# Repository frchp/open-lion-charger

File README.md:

# open-lion-charger
Open source battery charger and discharger

Based on [private archived project](https://github.com/frchp/li-ion-battery-high-current-charger)

TODO :
  1. Manufacturing
  2. Arduino software/library for easy integration

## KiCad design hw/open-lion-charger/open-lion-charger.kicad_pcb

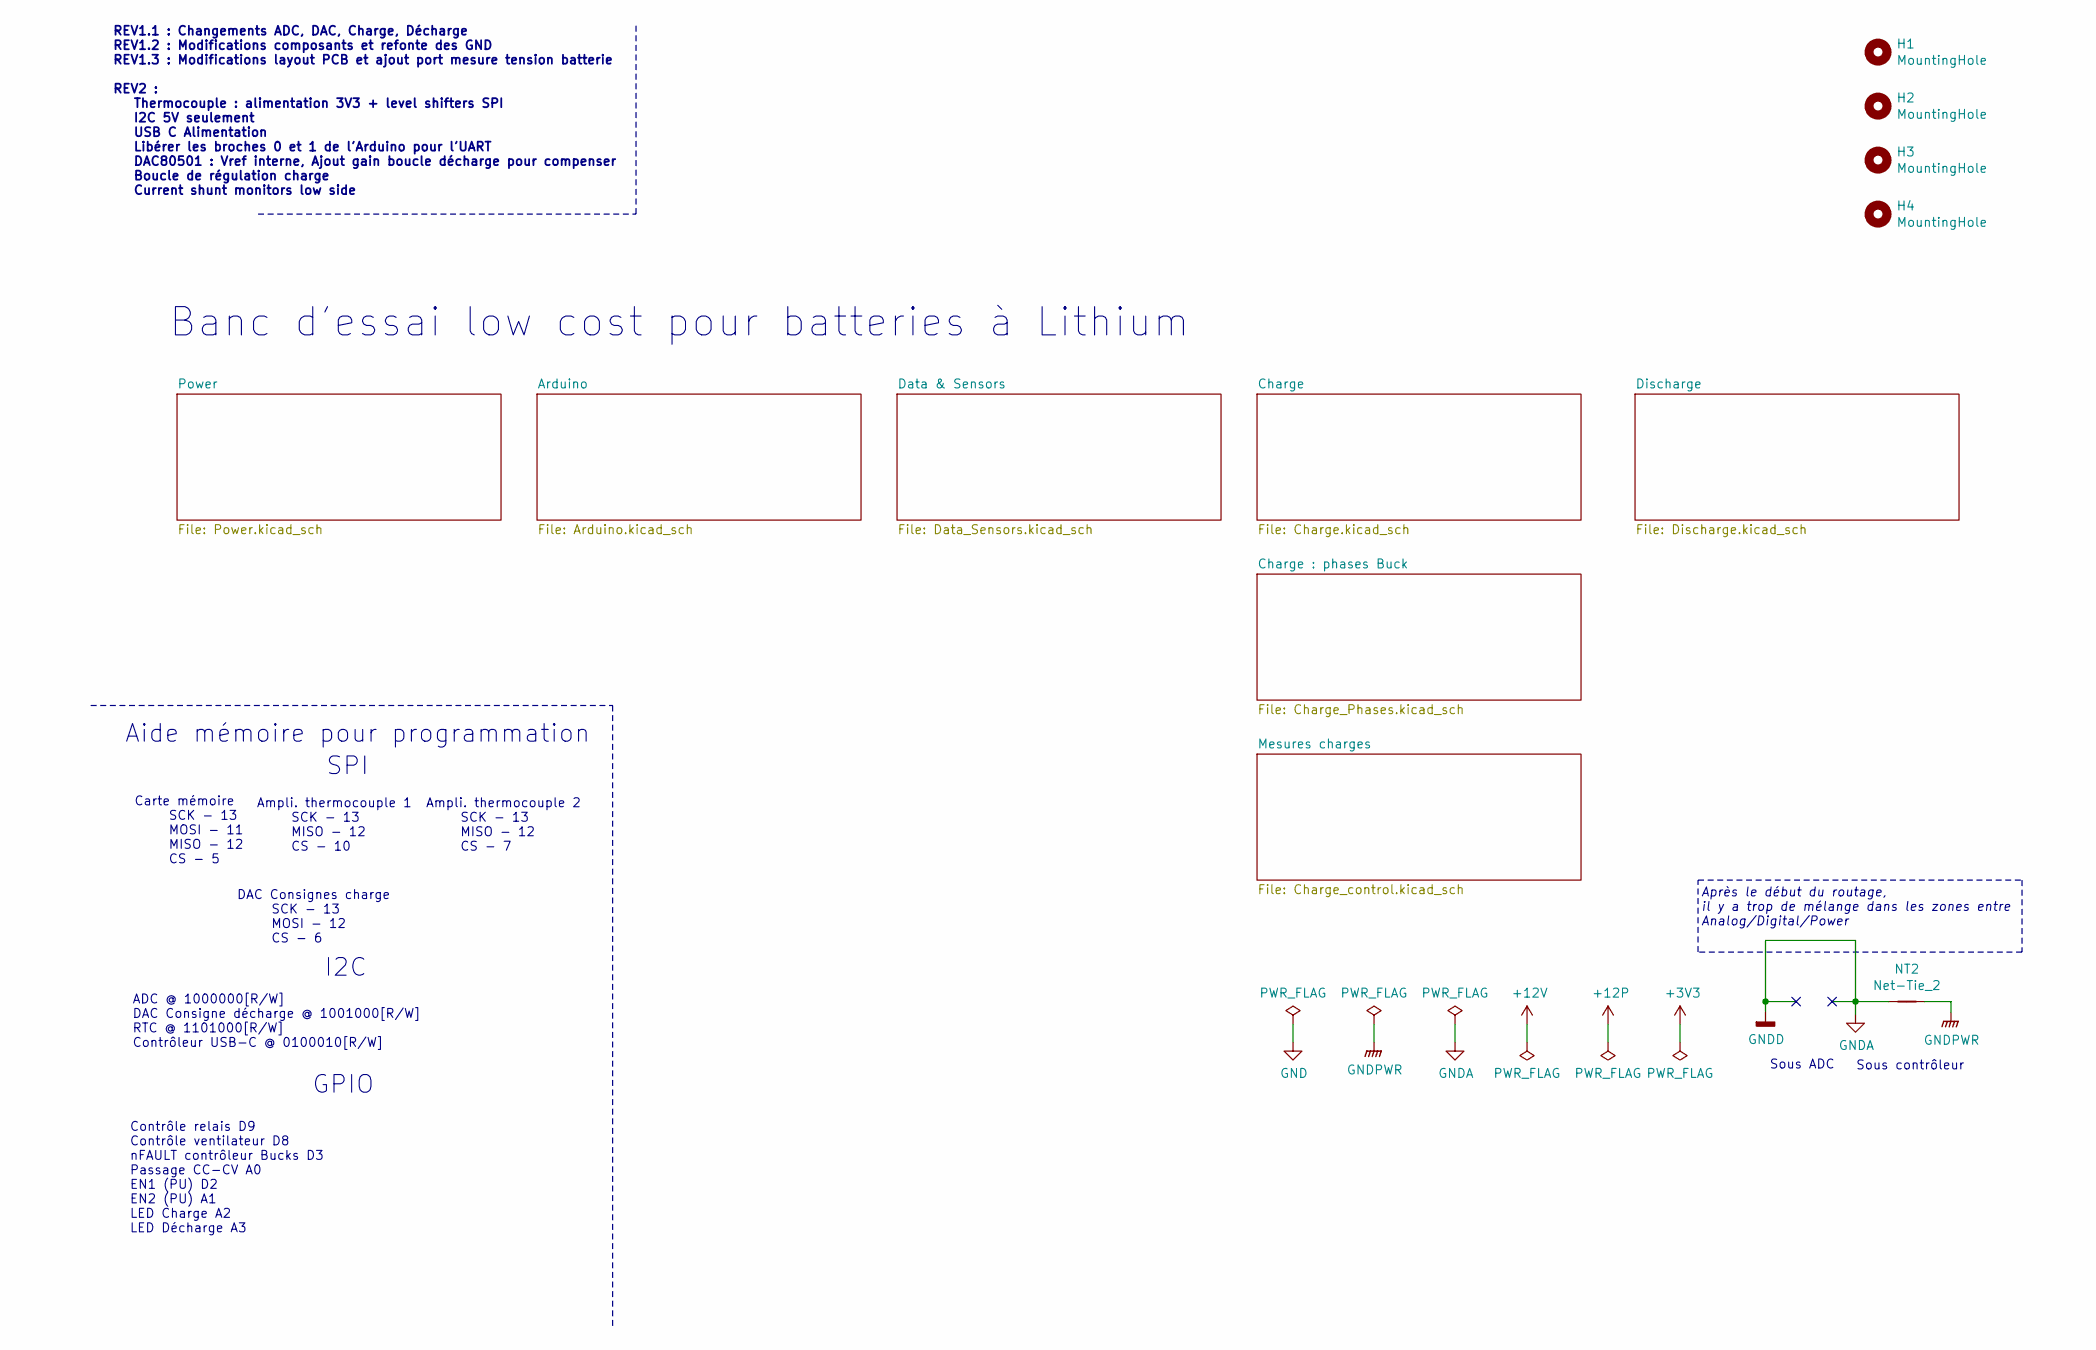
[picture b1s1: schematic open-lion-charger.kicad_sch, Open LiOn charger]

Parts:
H1, H2, H3, H4: MountingHole; MountingHole_3.2mm_M3_ISO7380
NT2: Net-Tie_2; NetTie-2_SMD_Pad0.5mm

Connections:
GNDA: NT2.1; also elsewhere on the board
GNDPWR: NT2.2; also elsewhere on the board

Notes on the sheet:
Carte mémoire SCK - 13 MOSI - 11 MISO - 12 CS - 5
Ampli. thermocouple 1 SCK - 13 MISO - 12 CS - 10
I2C
Ampli. thermocouple 2 SCK - 13 MISO - 12 CS - 7
REV1.1 : Changements ADC, DAC, Charge, Décharge REV1.2 : Modifications composants et refonte des GND REV1.3 : Modifications layout PCB et ajout port mesure tension batterie REV2 : Thermocouple : alimentation 3V3 + level shifters SPI I2C 5V seulement USB C Alimentation Libérer les broches 0 et 1 de 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
GPIO
Sous contrôleur
DAC Consignes charge SCK - 13 MOSI - 12 CS - 6
Aide mémoire pour programmation
ADC @ 1000000[R/W] DAC Consigne décharge @ 1001000[R/W] RTC @ 1101000[R/W] Contrôleur USB-C @ 0100010[R/W]
Sous ADC
SPI
Contrôle relais D9 Contrôle ventilateur D8 nFAULT contrôleur Bucks D3 Passage CC-CV A0 EN1 (PU) D2 EN2 (PU) A1 LED Charge A2 LED Décharge A3
Après le début du routage, il y a trop de mélange dans les zones entre Analog/Digital/Power
Banc d'essai low cost pour batteries à Lithium

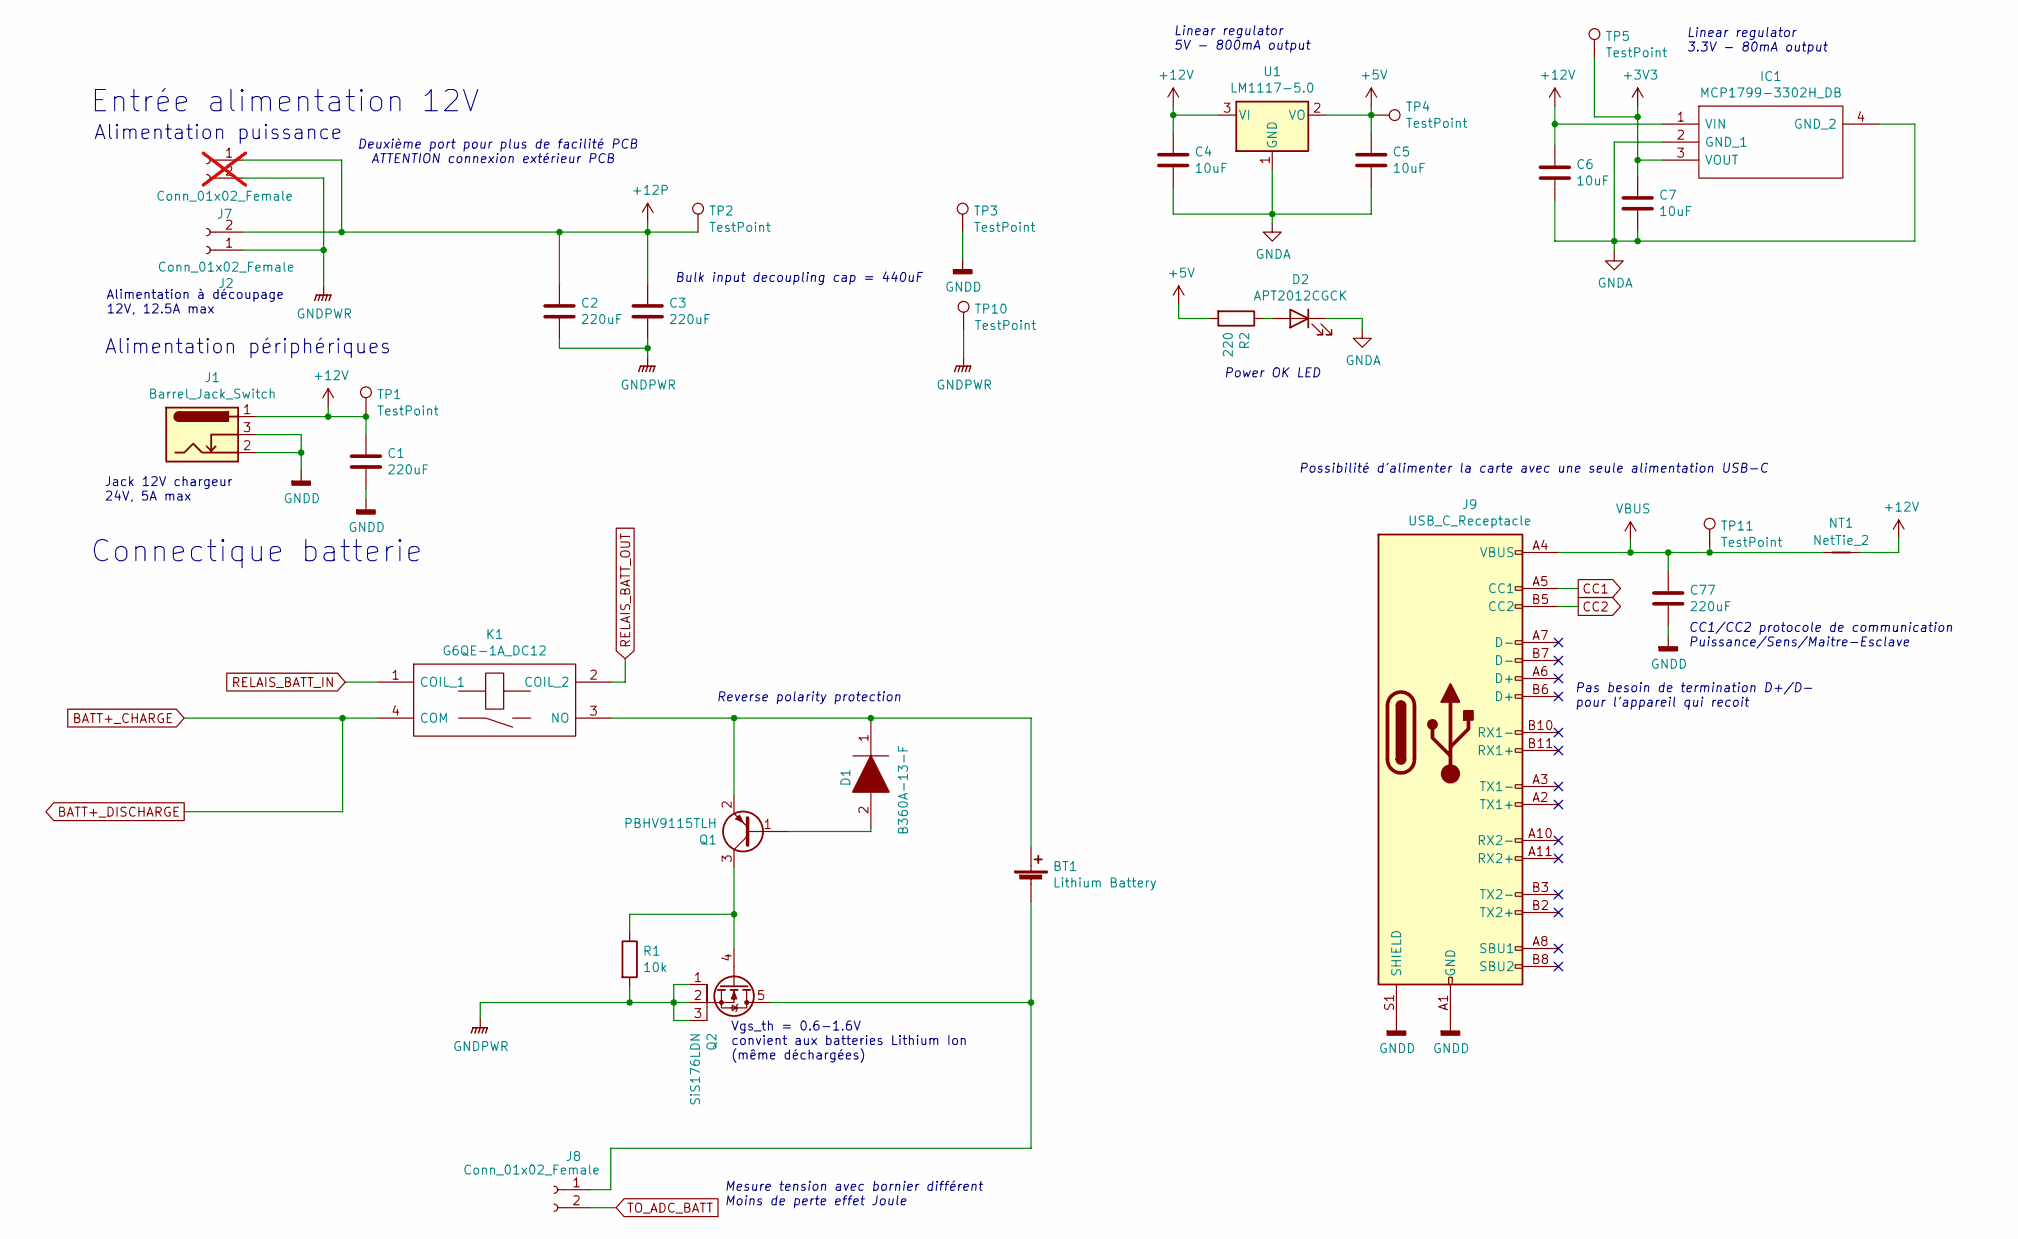
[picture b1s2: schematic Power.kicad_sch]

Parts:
BT1: Lithium Battery; TerminalBlock_bornier-2_P5.08mm
C1, C2, C3, C77: 220uF; CP_EIA-7343-31_Kemet-D_Pad2.25x2.55mm_HandSolder
C4, C5, C6, C7: 10uF; C_0805_2012Metric
D1: B360A-13-F; DIOM5226X240N; Manufacturer_Part_Number B360A-13-F; Mouser Part Number 621-B360A-F
D2: APT2012CGCK; LED_0805_2012Metric_Pad1.15x1.40mm_HandSolder
IC1: MCP1799-3302H_DB; SOT230P700X180-4N; Manufacturer_Part_Number MCP1799-3302H/DB; Mouser Part Number 579-MCP1799-3302H/DB
J1: Barrel_Jack_Switch; BarrelJack_Wuerth_6941xx301002
J2, J8: Conn_01x02_Female; TerminalBlock_bornier-2_P5.08mm
J7: Conn_01x02_Female; TerminalBlock_bornier-2_P5.08mm; not fitted
J9: USB_C_Receptacle; USB_C_Receptacle_GCT_USB4085
K1: G6QE-1A_DC12; G6QE1ADC12; Manufacturer_Part_Number G6QE-1A DC12; Mouser Part Number 653-G6QE-1ADC12
NT1: NetTie_2; R_2816_7142Metric_Pad3.20x4.45mm_HandSolder
Q1: PBHV9115TLH; SOT-23
Q2: SiS176LDN; Vishay_PowerPAK_1212-8_Single
R1: 10k; R_0805_2012Metric
R2: 220; R_0805_2012Metric
TP1, TP2, TP3, TP4, TP5, TP10, TP11: TestPoint; TestPoint_Keystone_5000-5004_Miniature
U1: LM1117-5.0; SOT-223

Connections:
+3V3: C7.1, IC1.3 (VOUT), TP5.1; also elsewhere on the board
+5V: C5.1, R2.2, TP4.1, U1.2 (VO); also elsewhere on the board
+12P: C2.1, C3.1, J2.2, J7.1, TP2.1; also elsewhere on the board
BATT+_CHARGE: K1.4 (COM); also elsewhere on the board
CC1: J9.A5 (CC1); also elsewhere on the board
CC2: J9.B5 (CC2); also elsewhere on the board
GNDA: C1.2, C4.2, C5.2, C6.2, C7.2, C77.2, D2.1 (K), IC1.2 (GND_1), IC1.4 (GND_2), J1.2, J1.3, J9.A1 (GND), J9.A12 (GND), J9.B1 (GND), J9.B12 (GND), J9.S1 (SHIELD), TP3.1, U1.1 (GND); also elsewhere on the board
GNDPWR: C2.2, C3.2, J2.1, J7.2, Q2.1, Q2.2, Q2.3, R1.2, TP10.1; also elsewhere on the board
unnamed: BT1.1 (+), D1.1, K1.3 (NO), Q1.2 (E)
unnamed: BT1.2 (-), J8.1, Q2.5
unnamed: D2.2 (A), R2.1
unnamed: D1.2, Q1.1 (B)
unnamed: Q1.3 (C), Q2.4, R1.1
RELAIS_BATT_IN: K1.1 (COIL_1); also elsewhere on the board
RELAIS_BATT_OUT: C1.1, C4.1, C6.1, IC1.1 (VIN), J1.1, K1.2 (COIL_2), NT1.2, TP1.1, U1.3 (VI); also elsewhere on the board
TO_ADC_BATT: J8.2; also elsewhere on the board
VBUS: C77.1, J9.A4 (VBUS), J9.A9 (VBUS), J9.B4 (VBUS), J9.B9 (VBUS), NT1.1, TP11.1; also elsewhere on the board

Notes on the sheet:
Alimentation à découpage 12V, 12.5A max
Connectique batterie
Entrée alimentation 12V
Deuxième port pour plus de facilité PCB ATTENTION connexion extérieur PCB
Bulk input decoupling cap = 440uF
CC1/CC2 protocole de communication Puissance/Sens/Maitre-Esclave
Alimentation périphériques
Jack 12V chargeur 24V, 5A max
Power OK LED
Pas besoin de termination D+/D- pour l'appareil qui recoit
Vgs_th = 0.6-1.6V convient aux batteries Lithium Ion (même déchargées)
Alimentation puissance
Mesure tension avec bornier différent Moins de perte effet Joule
Linear regulator 5V - 800mA output
Reverse polarity protection
Possibilité d'alimenter la carte avec une seule alimentation USB-C
Linear regulator 3.3V - 80mA output

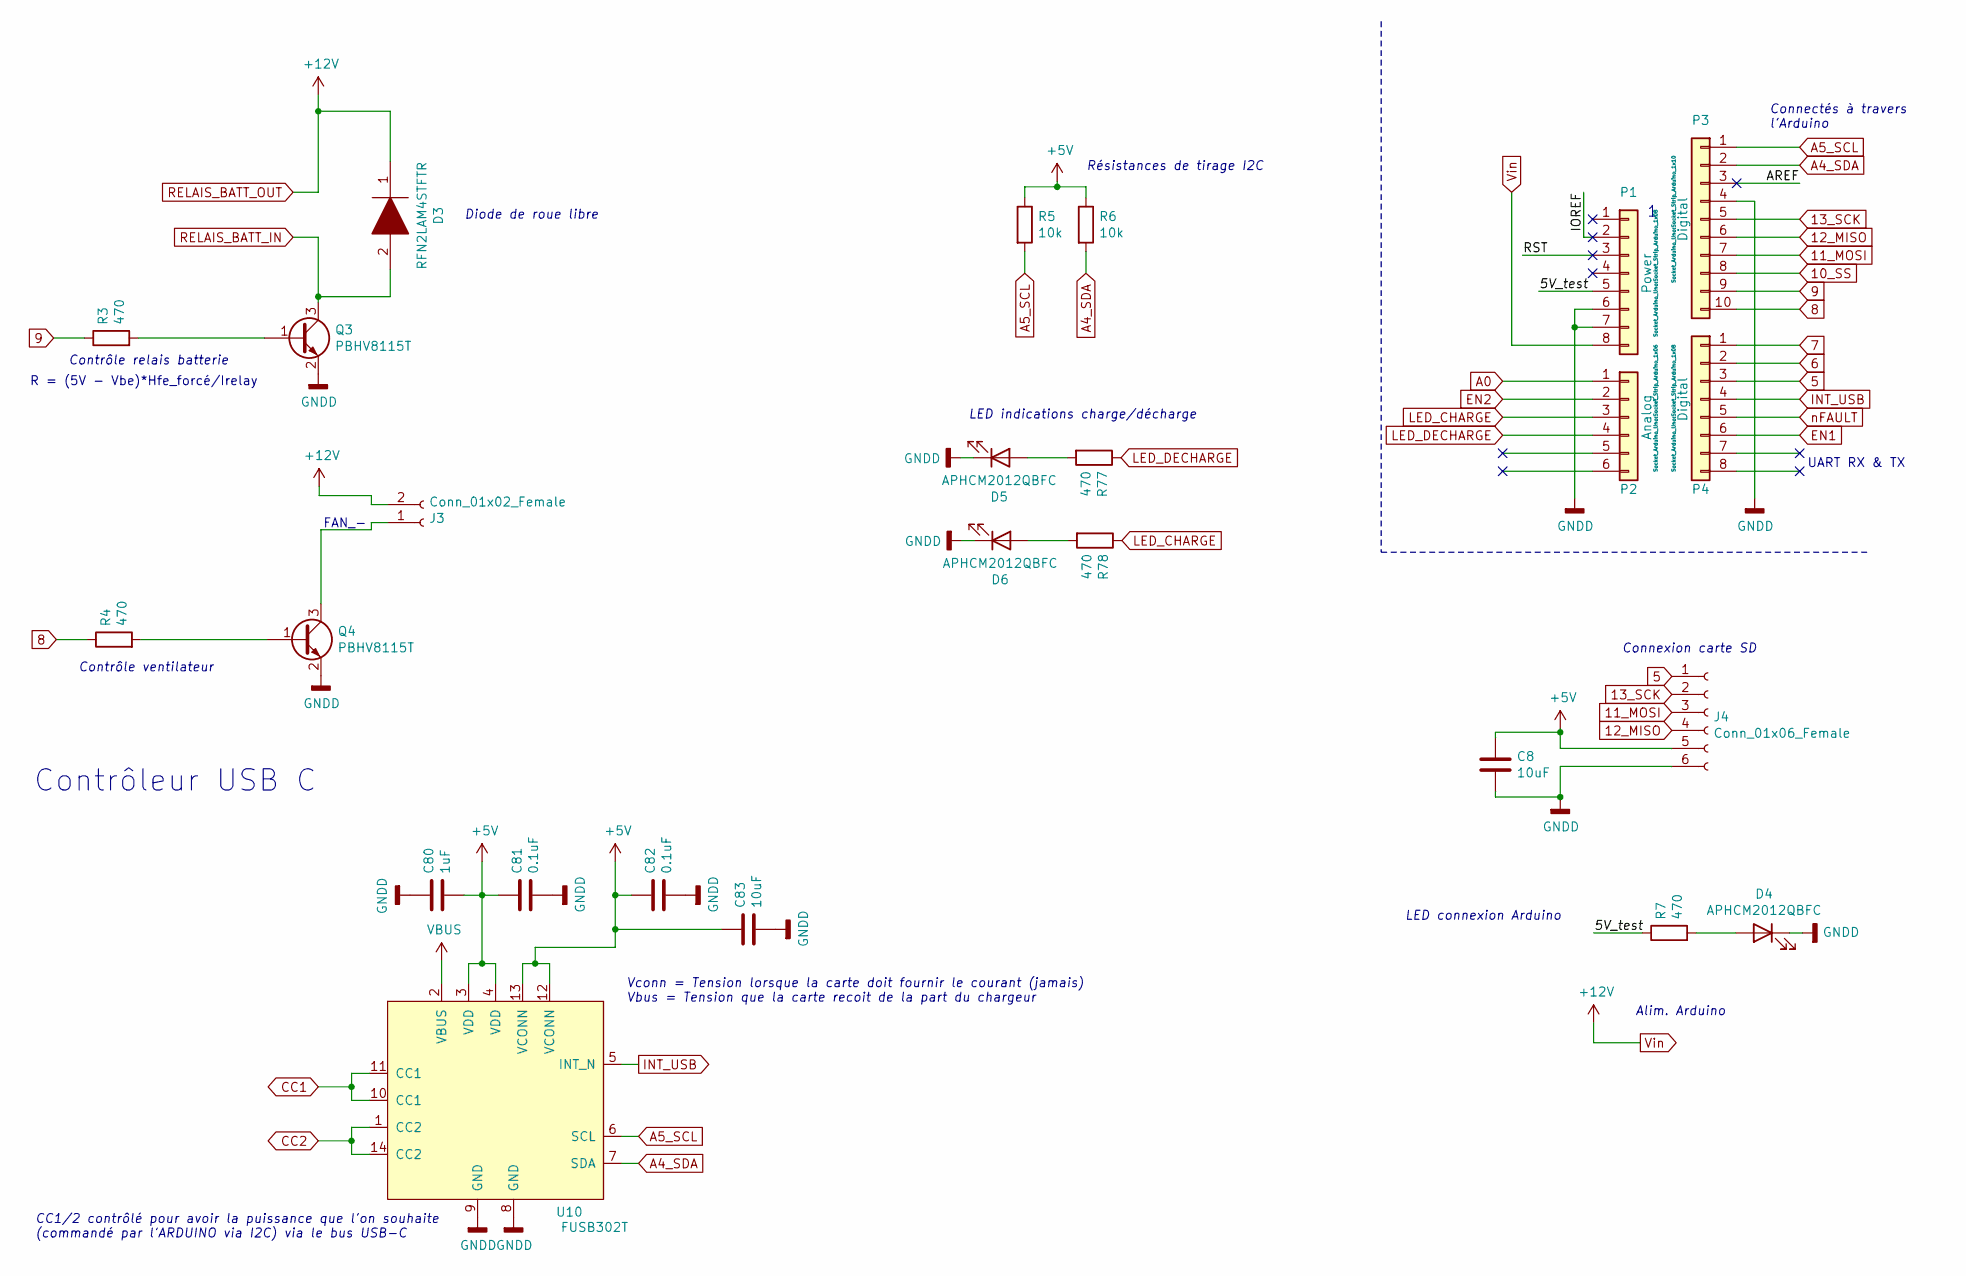
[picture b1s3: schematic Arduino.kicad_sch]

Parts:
C8, C83: 10uF; C_0805_2012Metric
C80: 1uF; C_0805_2012Metric
C81, C82: 0.1uF; C_0805_2012Metric
D3: RFN2LAM4STFTR; SODFL4725X105N; Manufacturer_Part_Number RFN2LAM4STFTR; Mouser Part Number 755-RFN2LAM4STFTR
D4, D5, D6: APHCM2012QBFC; LED_0805_2012Metric_Pad1.15x1.40mm_HandSolder
J3: Conn_01x02_Female; TerminalBlock_bornier-2_P5.08mm
J4: Conn_01x06_Female; PinSocket_1x06_P2.54mm_Vertical
P1: Power; Socket_Strip_Arduino_1x08
P2: Analog; Socket_Strip_Arduino_1x06
P3: Digital; Socket_Strip_Arduino_1x10
P4: Digital; Socket_Strip_Arduino_1x08
Q3, Q4: PBHV8115T; SOT-23
R3, R4, R7, R77, R78: 470; R_0805_2012Metric
R5, R6: 10k; R_0805_2012Metric
U10: FUSB302T; WQFN-14-1EP_2.5x2.5mm_P0.5mm_EP1.45x1.45mm

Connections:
5: J4.1, P4.3
6: P4.2; also elsewhere on the board
7: P4.1; also elsewhere on the board
8: P3.10, R4.1
9: P3.9, R3.1
10_SS: P3.8; also elsewhere on the board
11_MOSI: J4.3, P3.7; also elsewhere on the board
12_MISO: J4.4, P3.6; also elsewhere on the board
13_SCK: J4.2, P3.5; also elsewhere on the board
+5V: C8.1, C80.2, C81.1, C82.1, C83.1, J4.5, R5.1, R6.1, U10.3 (VDD), U10.4 (VDD), U10.12 (VCONN), U10.13 (VCONN); also elsewhere on the board
/Arduino/5V_test: P1.5, R7.1
/Arduino/AREF: P3.3
/Arduino/IOREF: P1.2
/Arduino/RST: P1.3
A0: P2.1; also elsewhere on the board
A4_SDA: P3.2, R6.2, U10.7 (SDA); also elsewhere on the board
A5_SCL: P3.1, R5.2, U10.6 (SCL); also elsewhere on the board
CC1: U10.10 (CC1), U10.11 (CC1); also elsewhere on the board
CC2: U10.1 (CC2), U10.14 (CC2); also elsewhere on the board
EN1: P4.6; also elsewhere on the board
EN2: P2.2; also elsewhere on the board
GNDA: C8.2, C80.1, C81.2, C82.2, C83.2, D4.1 (K), D5.1 (K), D6.1 (K), J4.6, P1.6, P1.7, P3.4, Q3.2 (E), Q4.2 (E), U10.8 (GND), U10.9 (GND); also elsewhere on the board
INT_USB: P4.4, U10.5 (INT_N)
LED_CHARGE: P2.3, R78.1
LED_DECHARGE: P2.4, R77.1
unnamed: D4.2 (A), R7.2
unnamed: D5.2 (A), R77.2
unnamed: D6.2 (A), R78.2
unnamed: J3.1, Q4.3 (C)
unnamed: Q3.1 (B), R3.2
unnamed: Q4.1 (B), R4.2
RELAIS_BATT_IN: D3.2, Q3.3 (C); also elsewhere on the board
RELAIS_BATT_OUT: D3.1, J3.2, P1.8; also elsewhere on the board
VBUS: U10.2 (VBUS); also elsewhere on the board
nFAULT: P4.5; also elsewhere on the board

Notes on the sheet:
FAN_-
Alim. Arduino
Diode de roue libre
Contrôleur USB C
Connexion carte SD
Résistances de tirage I2C
R = (5V - Vbe)*Hfe_forcé/Irelay
LED indications charge/décharge
LED connexion Arduino
Vconn = Tension lorsque la carte doit fournir le courant (jamais) Vbus = Tension que la carte recoit de la part du chargeur
Connectés à travers l'Arduino
CC1/2 contrôlé pour avoir la puissance que l'on souhaite (commandé par l'ARDUINO via I2C) via le bus USB-C
Contrôle relais batterie
Contrôle ventilateur
UART RX & TX

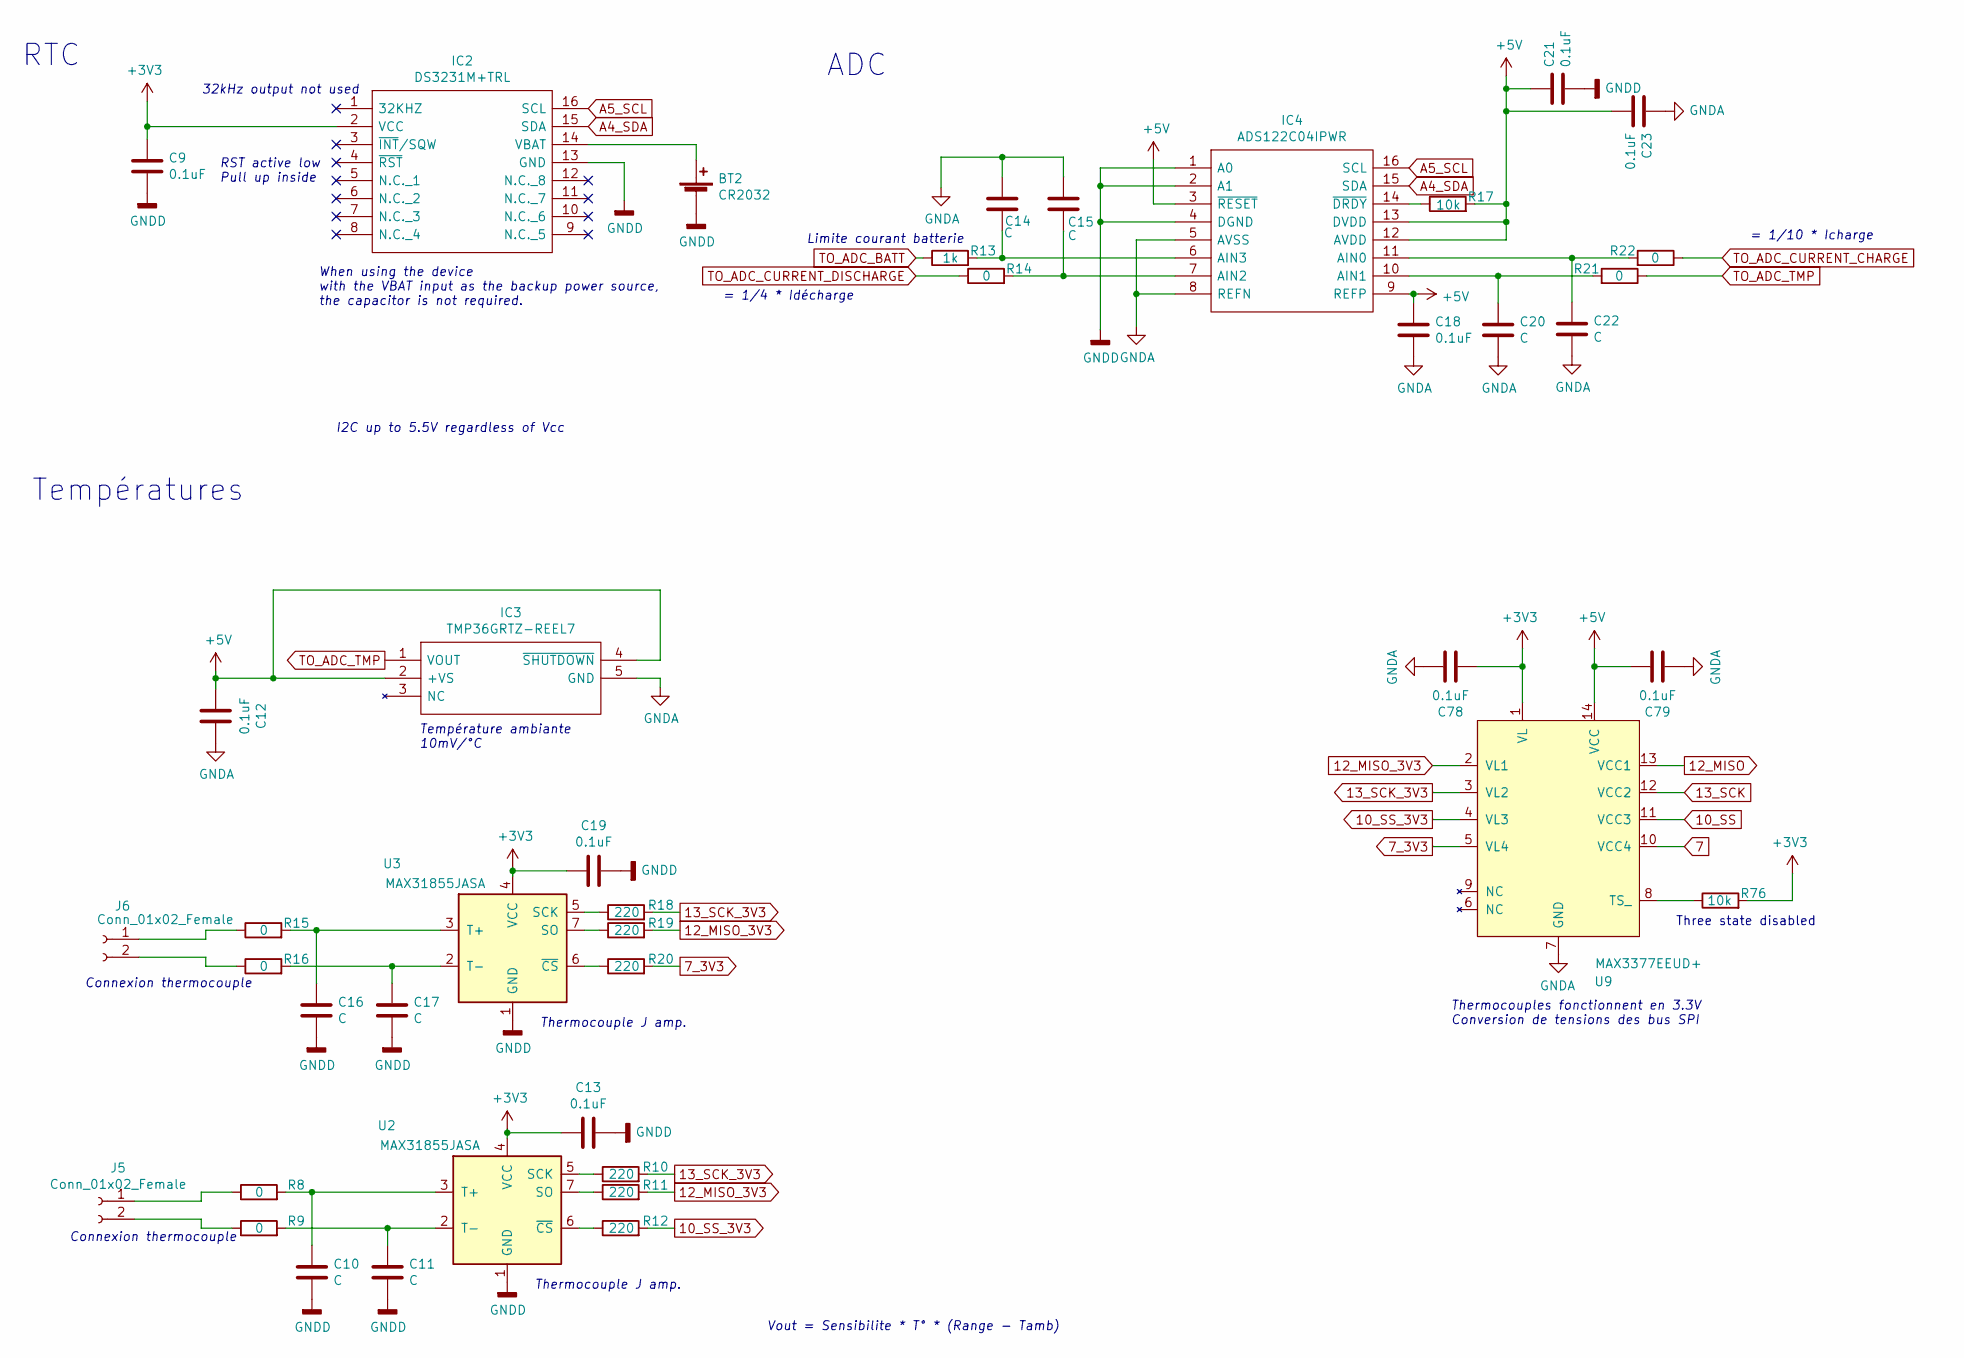
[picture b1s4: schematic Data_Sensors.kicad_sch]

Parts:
BT2: CR2032; BATHLD001TR
C9, C12, C13, C18, C19, C21, C23, C78, C79: 0.1uF; C_0805_2012Metric
C10, C11, C14, C15, C16, C17, C20, C22: C; C_0805_2012Metric
IC2: DS3231M+TRL; SOIC127P1032X265-16N; Manufacturer_Part_Number DS3231M+TRL; Mouser Part Number 700-DS3231M+TRL
IC3: TMP36GRTZ-REEL7; SOT95P280X145-5N; Manufacturer_Part_Number TMP36GRTZ-REEL7; Mouser Part Number 584-TMP36GRTZ-R7
IC4: ADS122C04IPWR; SOP65P640X120-16N; Manufacturer_Part_Number ADS122C04IPWR; Mouser Part Number 595-ADS122C04IPWR
J5, J6: Conn_01x02_Female; PinSocket_2x01_P1.27mm_Vertical
R8, R9, R14, R15, R16, R21, R22: 0; R_0805_2012Metric
R10, R11, R12, R18, R19, R20: 220; R_0805_2012Metric
R13: 1k; R_0805_2012Metric
R17, R76: 10k; R_0805_2012Metric
U2, U3: MAX31855JASA; SOIC-8_3.9x4.9mm_P1.27mm
U9: MAX3377EEUD+; TSSOP-14_4.4x5mm_P0.65mm

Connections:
7: U9.10 (VCC4); also elsewhere on the board
7_3V3: R20.2, U9.5 (VL4)
10_SS: U9.11 (VCC3); also elsewhere on the board
10_SS_3V3: R12.2, U9.4 (VL3)
12_MISO: U9.13 (VCC1); also elsewhere on the board
12_MISO_3V3: R11.2, R19.2, U9.2 (VL1)
13_SCK: U9.12 (VCC2); also elsewhere on the board
13_SCK_3V3: R10.2, R18.2, U9.3 (VL2)
+3V3: C9.1, C13.2, C19.2, C78.2, IC2.2 (VCC), R76.2, U2.4 (VCC), U3.4 (VCC), U9.1 (VL); also elsewhere on the board
+5V: C12.2, C18.1, C21.1, C23.2, C79.2, IC3.2 (+VS), IC3.4 (~SHUTDOWN), IC4.3 (~RESET), IC4.9 (REFP), IC4.12 (AVDD), IC4.13 (DVDD), R17.2, U9.14 (VCC); also elsewhere on the board
A4_SDA: IC2.15 (SDA), IC4.15 (SDA); also elsewhere on the board
A5_SCL: IC2.16 (SCL), IC4.16 (SCL); also elsewhere on the board
FB_COURANT: R14.1; also elsewhere on the board
GNDA: BT2.2 (-), C9.2, C10.1, C11.1, C12.1, C13.1, C14.2, C15.2, C16.1, C17.1, C18.2, C19.1, C20.1, C21.2, C22.1, C23.1, C78.1, C79.1, IC2.13 (GND), IC3.5 (GND), IC4.1 (A0), IC4.2 (A1), IC4.4 (DGND), IC4.5 (AVSS), IC4.8 (REFN), U2.1 (GND), U3.1 (GND), U9.7 (GND); also elsewhere on the board
unnamed: BT2.1 (+), IC2.14 (VBAT)
unnamed: C22.2, IC4.11 (AIN0), R22.2
unnamed: C20.2, IC4.10 (AIN1), R21.2
unnamed: C15.1, IC4.7 (AIN2), R14.2
unnamed: C14.1, IC4.6 (AIN3), R13.2
unnamed: IC4.14 (~DRDY), R17.1
unnamed: J5.1, R8.1
unnamed: J5.2, R9.1
unnamed: J6.1, R15.1
unnamed: J6.2, R16.1
unnamed: R10.1, U2.5 (SCK)
unnamed: R11.1, U2.7 (SO)
unnamed: C10.2, R8.2, U2.3 (T+)
unnamed: C11.2, R9.2, U2.2 (T-)
unnamed: R12.1, U2.6 (~CS)
unnamed: R18.1, U3.5 (SCK)
unnamed: R19.1, U3.7 (SO)
unnamed: C16.2, R15.2, U3.3 (T+)
unnamed: C17.2, R16.2, U3.2 (T-)
unnamed: R20.1, U3.6 (~CS)
unnamed: R76.1, U9.8 (TS_)
TO_ADC_BATT: R13.1; also elsewhere on the board
TO_ADC_CURRENT_CHARGE: R22.1; also elsewhere on the board
TO_ADC_TMP: IC3.1 (VOUT), R21.1

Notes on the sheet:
Limite courant batterie
ADC
= 1/4 * Idécharge
Thermocouple J amp.
Connexion thermocouple
RTC
Température ambiante 10mV/°C
32kHz output not used
When using the device with the VBAT input as the backup power source, the capacitor is not required.
I2C up to 5.5V regardless of Vcc
Températures
Three state disabled
Thermocouples fonctionnent en 3.3V Conversion de tensions des bus SPI
= 1/10 * Icharge
Vout = Sensibilite * T° * (Range - Tamb)
RST active low Pull up inside

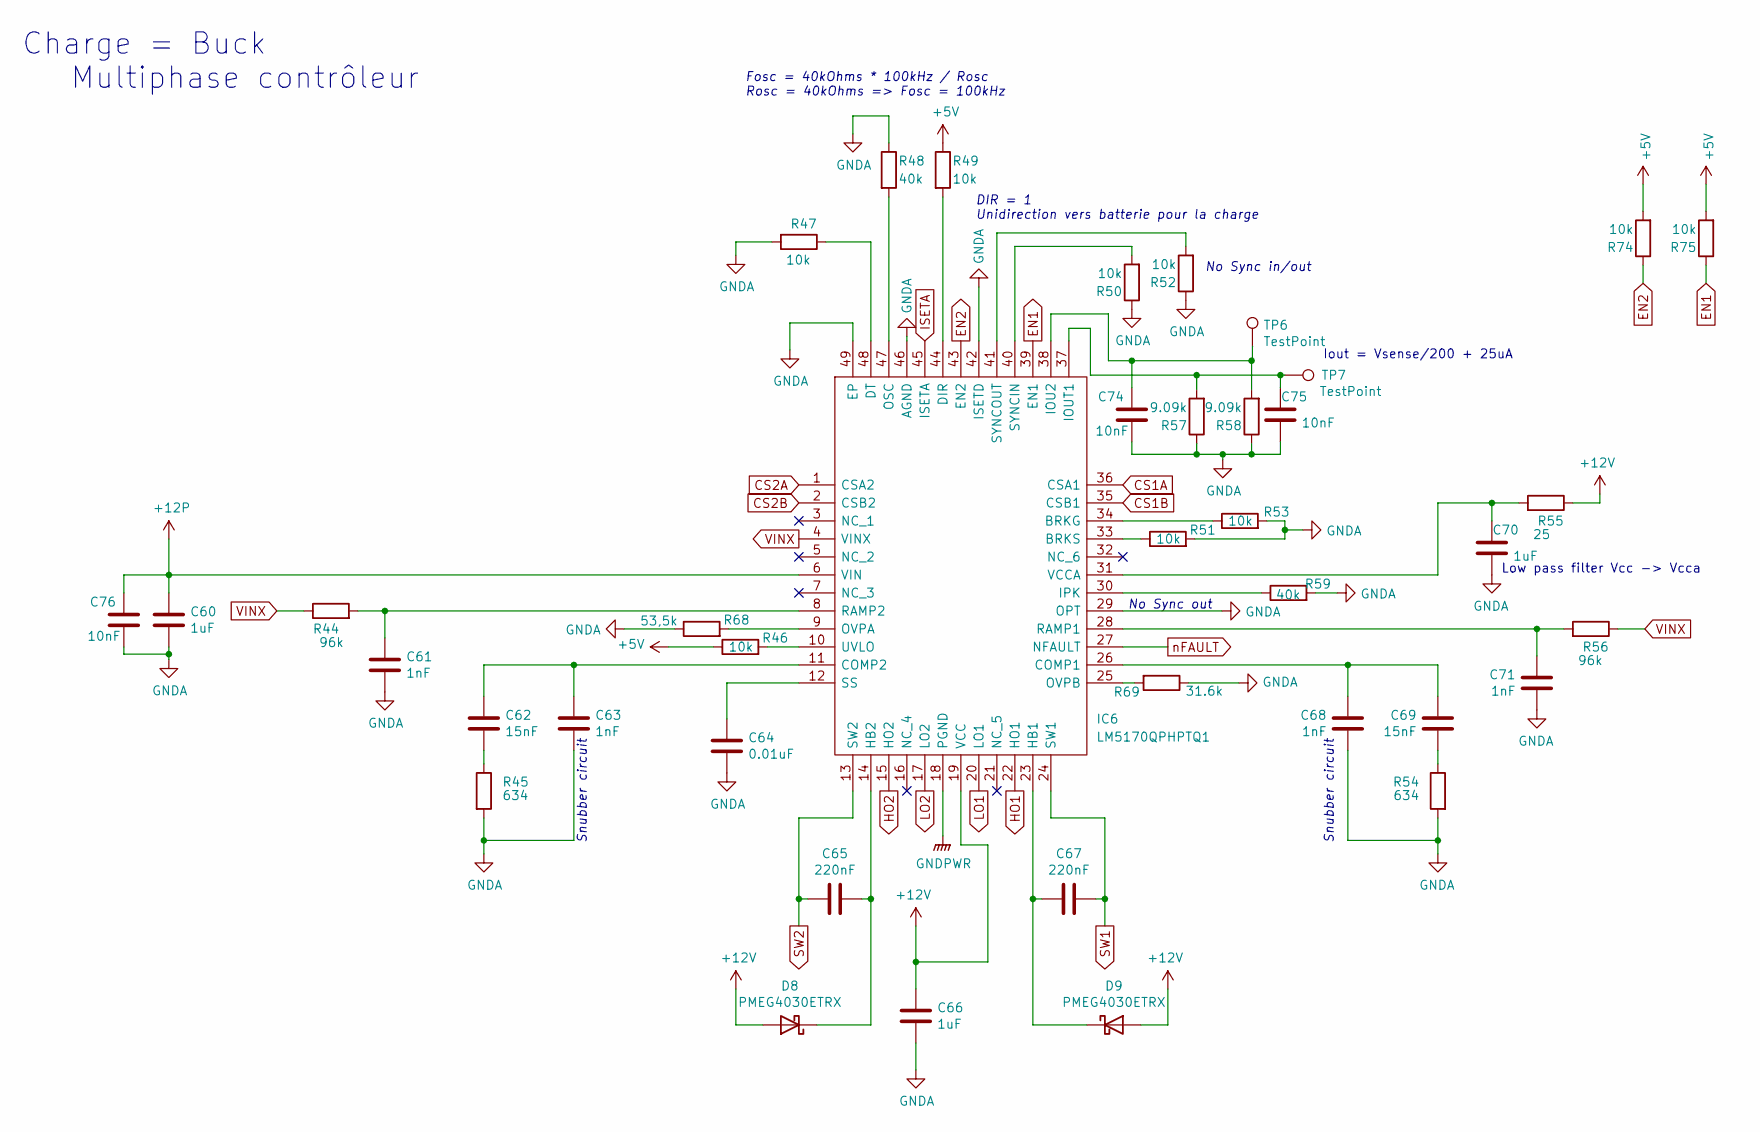
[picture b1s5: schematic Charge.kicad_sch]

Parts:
C60, C66, C70: 1uF; C_0805_2012Metric
C61, C63, C68, C71: 1nF; C_0805_2012Metric
C62, C69: 15nF; C_0805_2012Metric
C64: 0.01uF; C_0805_2012Metric
C65, C67: 220nF; C_0805_2012Metric
C74, C75, C76: 10nF; C_0805_2012Metric
D8, D9: PMEG4030ETRX; SODFL4725X105N
IC6: LM5170QPHPTQ1; QFP50P900X900X120-49N; Manufacturer_Part_Number LM5170QPHPTQ1; Mouser Part Number 595-LM5170QPHPTQ1
R44, R56: 96k; R_0805_2012Metric
R45, R54: 634; R_0805_2012Metric
R46, R47, R49, R50, R51, R52, R53, R74, R75: 10k; R_0805_2012Metric
R48, R59: 40k; R_0805_2012Metric
R55: 25; R_0805_2012Metric
R57, R58: 9.09k; R_0805_2012Metric
R68: 53,5k; R_0805_2012Metric
R69: 31.6k; R_0805_2012Metric
TP6, TP7: TestPoint; TestPoint_Keystone_5000-5004_Miniature

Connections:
+5V: R46.1, R49.1, R74.2, R75.2; also elsewhere on the board
+12P: C60.1, C76.1, IC6.6 (VIN); also elsewhere on the board
CS1A: IC6.36 (CSA1); also elsewhere on the board
CS1B: IC6.35 (CSB1); also elsewhere on the board
CS2A: IC6.1 (CSA2); also elsewhere on the board
CS2B: IC6.2 (CSB2); also elsewhere on the board
EN1: IC6.39 (EN1), R75.1; also elsewhere on the board
EN2: IC6.43 (EN2), R74.1; also elsewhere on the board
GNDA: C60.2, C61.2, C63.2, C64.2, C66.2, C68.2, C70.2, C71.2, C74.2, C75.2, C76.2, IC6.29 (OPT), IC6.42 (ISETD), IC6.46 (AGND), IC6.49 (EP), R45.2, R47.2, R48.1, R50.1, R51.2, R52.1, R53.2, R54.2, R57.1, R58.1, R59.2, R68.1, R69.1; also elsewhere on the board
GNDPWR: IC6.18 (PGND); also elsewhere on the board
HO1: IC6.22 (HO1); also elsewhere on the board
HO2: IC6.15 (HO2); also elsewhere on the board
ISETA: IC6.45 (ISETA); also elsewhere on the board
LO1: IC6.20 (LO1); also elsewhere on the board
LO2: IC6.17 (LO2); also elsewhere on the board
unnamed: C62.2, R45.1
unnamed: C69.2, R54.1
unnamed: C65.2, D8.1 (K), IC6.14 (HB2)
unnamed: C67.2, D9.1 (K), IC6.23 (HB1)
unnamed: IC6.34 (BRKG), R53.1
unnamed: IC6.33 (BRKS), R51.1
unnamed: C68.1, C69.1, IC6.26 (COMP1)
unnamed: C62.1, C63.1, IC6.11 (COMP2)
unnamed: IC6.44 (DIR), R49.2
unnamed: IC6.48 (DT), R47.1
unnamed: C74.1, IC6.38 (IOU2), R58.2, TP6.1
unnamed: C75.1, IC6.37 (IOUT1), R57.2, TP7.1
unnamed: IC6.30 (IPK), R59.1
unnamed: IC6.47 (OSC), R48.2
unnamed: IC6.9 (OVPA), R68.2
unnamed: IC6.25 (OVPB), R69.2
unnamed: C71.1, IC6.28 (RAMP1), R56.2
unnamed: C61.1, IC6.8 (RAMP2), R44.2
unnamed: C64.1, IC6.12 (SS)
unnamed: IC6.40 (SYNCIN), R50.2
unnamed: IC6.41 (SYNCOUT), R52.2
unnamed: IC6.10 (UVLO), R46.2
unnamed: C70.1, IC6.31 (VCCA), R55.2
RELAIS_BATT_OUT: C66.1, D8.2 (A), D9.2 (A), IC6.19 (VCC), R55.1; also elsewhere on the board
SW1: C67.1, IC6.24 (SW1); also elsewhere on the board
SW2: C65.1, IC6.13 (SW2); also elsewhere on the board
VINX: IC6.4 (VINX), R44.1, R56.1
nFAULT: IC6.27 (NFAULT); also elsewhere on the board

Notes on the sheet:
Snubber circuit
Iout = Vsense/200 + 25uA
DIR = 1 Unidirection vers batterie pour la charge
Fosc = 40kOhms * 100kHz / Rosc Rosc = 40kOhms => Fosc = 100kHz
Charge = Buck Multiphase contrôleur
Low pass filter Vcc -> Vcca
No Sync in/out
No Sync out

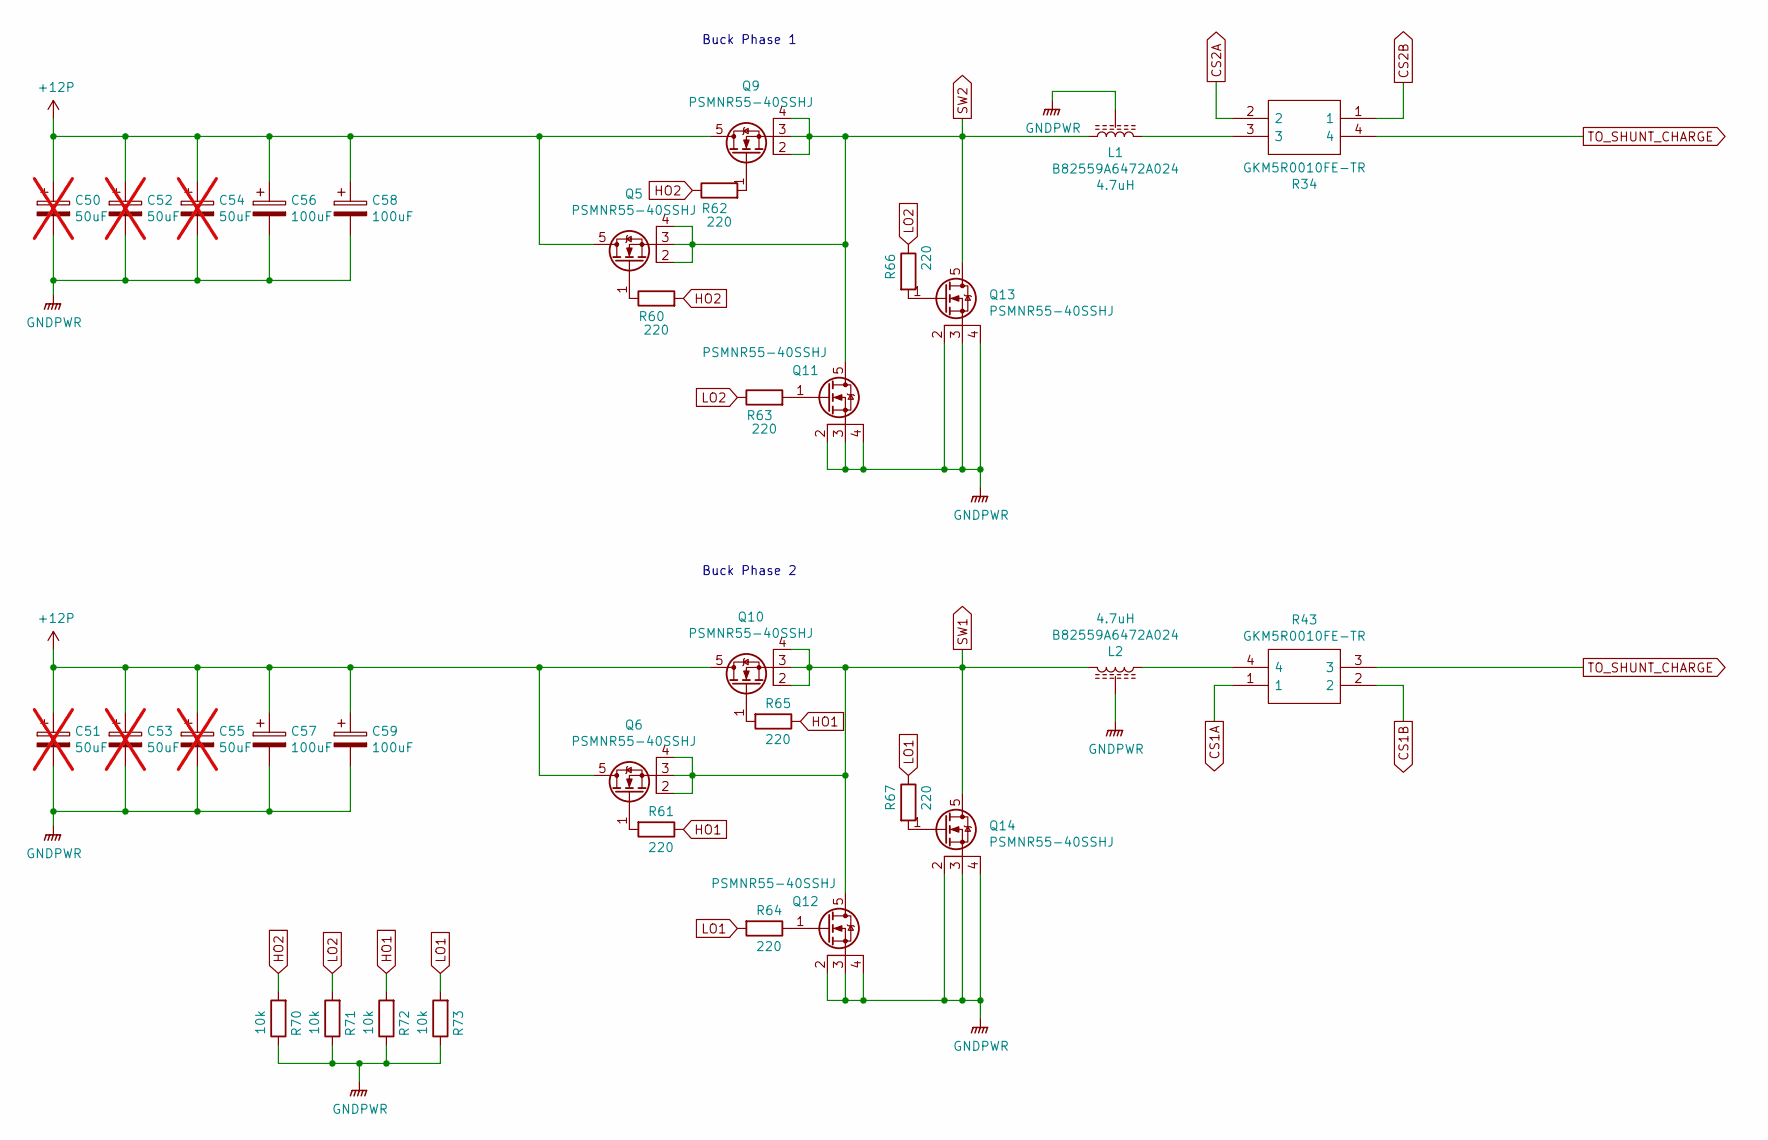
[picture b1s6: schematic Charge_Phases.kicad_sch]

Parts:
C50, C51, C52, C53, C54, C55: 50uF; SMD_Lytic_E; not fitted
C56, C57, C58, C59: 100uF; EEEFP0J331AV
L1, L2: B82559A6472A024
Q5, Q6, Q9, Q10, Q11, Q12, Q13, Q14: PSMNR55-40SSHJ; LFPAK88
R34, R43: GKM5R0010FE-TR; WSLP40261L000FEA; Manufacturer_Part_Number GKM5R0010FE-TR; Mouser Part Number 588-GKM5R0010FE-TR
R60, R61, R62, R63, R64, R65, R66, R67: 220; R_0805_2012Metric
R70, R71, R72, R73: 10k; R_0805_2012Metric

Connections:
+12P: C50.1, C51.1, C52.1, C53.1, C54.1, C55.1, C56.1, C57.1, C58.1, C59.1, Q5.5, Q6.5, Q9.5, Q10.5; also elsewhere on the board
CS1A: R43.1; also elsewhere on the board
CS1B: R43.2; also elsewhere on the board
CS2A: R34.2; also elsewhere on the board
CS2B: R34.1; also elsewhere on the board
GNDPWR: C50.2, C51.2, C52.2, C53.2, C54.2, C55.2, C56.2, C57.2, C58.2, C59.2, L1.3, L2.3, Q11.2, Q11.3, Q11.4, Q12.2, Q12.3, Q12.4, Q13.2, Q13.3, Q13.4, Q14.2, Q14.3, Q14.4, R70.1, R71.1, R72.1, R73.1; also elsewhere on the board
HO1: R61.1, R65.1, R72.2; also elsewhere on the board
HO2: R60.2, R62.1, R70.2; also elsewhere on the board
LO1: R64.2, R67.1, R73.2; also elsewhere on the board
LO2: R63.1, R66.1, R71.2; also elsewhere on the board
unnamed: L1.2, R34.3
unnamed: L2.1, R43.4
unnamed: Q5.1, R60.1
unnamed: Q6.1, R61.2
unnamed: Q9.1, R62.2
unnamed: Q10.1, R65.2
unnamed: Q11.1, R63.2
unnamed: Q12.1, R64.1
unnamed: Q13.1, R66.2
unnamed: Q14.1, R67.2
SW1: L2.2, Q6.2, Q6.3, Q6.4, Q10.2, Q10.3, Q10.4, Q12.5, Q14.5; also elsewhere on the board
SW2: L1.1, Q5.2, Q5.3, Q5.4, Q9.2, Q9.3, Q9.4, Q11.5, Q13.5; also elsewhere on the board
TO_SHUNT_CHARGE: R34.4, R43.3; also elsewhere on the board

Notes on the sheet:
Buck Phase 2
Buck Phase 1

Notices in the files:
parts and their libraries:
Copyright 2021 Accelerated Designs. All rights reserved.
